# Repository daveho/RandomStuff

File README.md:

# daveho hacks random stuff repository

This is the Git repository for my Random Stuff video series.

The subdirectories contain materials discussed in each episode.

Feedback is welcome, send email to <mailto:david.hovemeyer@gmail.com>

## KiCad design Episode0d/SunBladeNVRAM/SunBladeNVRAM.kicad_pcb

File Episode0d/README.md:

# Random Stuff, Episode 0xD

Link to video: <https://youtu.be/hTzB3pyzDiA>

In this episode, we investigate the
[M48T59Y](https://media.digikey.com/pdf/Data%20Sheets/ST%20Microelectronics%20PDFS/M48T59,Y_V.pdf)
nonvolatile RAM/RTC chip. This device was used in several Sun UltraSPARC workstations,
including a [Sun Blade](https://en.wikipedia.org/wiki/Sun_Blade_(workstation)) 150 which
I want to restore. Sun workstations use an NVRAM chip to store configuration information
such as the MAC address and boot options.  When the battery inside the device runs out,
this configuration information is lost.  Since these devices aren't manufactured any longer,
and haven't been for many years, some kind of replacement is needed.

## Replacement options

The Sun workstations (like my Sun Blade 150) used DIP-package
NVRAM/RTC chips. For the M48T59Y, this is the "-PC" variant.
These are basically just a standard 28-pin DIP device with a
plastic case on top containing the internal battery,
filled with potting compound (picture from EBay):

One replacement option involves grinding away the outer casing and potting compound
in order to expose the connections to the internal battery, soldering
wires to them, and connecting the wires to a coin cell battery holder
(click photos to embiggen):

There are two disadvantages to this approach:

1. It's annoying, time-consuming, and error-prone
2. Unless you're able to disconnect the internal battery embedded in the potting
   compound, the new coin cell battery could be drained trying to charge
   the dead internal battery

What I wanted was a replacement that could be assembled "from scratch", that
would have functionality equivalent to the original device.

Intriguingly, there is a surface-mount version of the chip that has "snap" connectors
for the battery and timing crystal, the "-MH" variant (picture from Amazon Japan):

In theory, you're supposed to use a separate
["SnapHAT" module](https://www.digikey.com/en/products/detail/stmicroelectronics/M4T28-BR12SH1/679615)
containing a battery and crystal, which snaps on top of the chip.
However, this still leaves you with the issue that the battery will
drain eventually, meaning you'll need to buy another SnapHAT, and
eventually these won't be manufactured any more. I really wanted
a solution with a proper coin cell battery holder so that I could
just replace the battery when I needed to.

My thought was that I could design a "stack" of small PCBs with the M48T59Y-70MH1,
a 32.768 kHz watch crystal, and header pins on the lower PCB, a coin cell
battery holder on the upper PCB, and stacking headers to join the two PCBs.
I was actually able to make this work:

Note that there are **significant compromises in the design of the lower PCB**,
and **it is fairly difficult to solder the components on the lower PCB**. I did eventually
arrive at an approach that works to some degree. The following document describes
the assembly steps (and also has the part list):

[Assembling the replacement module](assembly.md)

Also note that the M48T59Y-70MH1 is no longer available new, so you'll need to source
it from the usual secondary channels. I found some for a reasonable price from
a seller on AliExpress.

## Testing and programming

Just having an M48T59Y (either an original with the battery mod or my self-designed
replacement module) still leaves a couple of remaining issues:

* How do you know your M48T59Y is actually working correctly and retaining data
  when power is removed?
* How do you program the initial configuration information (such as the MAC
  address and hostid) into the device?

To address these issues, I designed and built a testing and programming circuit
using an Arduino Nano:

The [SunBladeNVRAMTest](SunBladeNVRAMTest) directory has the KiCad
project for the circuit. There is a [PDF of the schematic](SunBladeNVRAMTest/SunBladeNVRAMTest.pdf)
as well.

There are several Arduino sketches (just load the one you want to use into the
Arduino Nano.)

Before you can use the Arduino sketches, you need to "install" the
[m48t59y](m48t59y) library, which contains common definitions and functions
used by all of the sketches. To do so, either symlink or copy the
contents of the `m48t59y` directory into your `Arduino/libraries`
directory. On my Linux system, I did this by running the commands

```
cd ~/Arduino
mkdir -p libraries
cd libraries
ln -s ~/git/RandomStuff/Epidode0d/m48t59y
```

You should replace `~/git/RandomStuff` with the path to where you checked
out the [RandomStuff](https://github.com/daveho/RandomStuff/) repo.

If you're using Windows, then I believe your `Arduino` directory
will be in your `My Documents` folder. If you create a `libraries` folder
within the `Arduino` directory (if it doesn't already exist) and then copy
the `m48t59y` directory there, that should work.

These are the sketches:

* [Test\_M48T59Y/Test\_M48T59Y.ino](Test_M48T59Y/Test_M48T59Y.ino):
  the test sketch (press GO to start the test; if you hold down LOG when
  you press GO any data validation errors will be logged)
* [Dump\_M48T59Y/Dump\_M49T59Y.ino](Dump_M48T59Y/Dump_M48T59Y.ino):
  dump the NVRAM contents of an M48T59Y to serial output as a
  comma-separated list of hex values. Note that if you're using the
  Arduino 2.x IDE [it's not possible to copy all captured data
  from the serial monitor](https://github.com/arduino/arduino-ide/issues/1081)
  so you'll need to use an external program (e.g., minicom, tio, etc.) to capture
  the output.
* [Restore\_M48T59Y/Restore\_M48T59Y.ino](Restore_M48T59Y/Restore_M48T59Y.ino):
  restore data (stored in a PROGMEM byte array in the sketch) to the M48T59Y.
  Useful to replicate previously dumped data, e.g., reprogramming a device
  after changing the battery. *Hypothetically* you can edit the IDPROM
  data (the source code contains a working dump from a Sun Blade 100)
  and program it to an M48T59Y. The "GO" button writes data to an M48T59Y,
  and the "LOG" button just computes the IDPROM data checksum and
  prints it to the serial output.

Note that all of the sketches use 115200 as the serial baud rate.

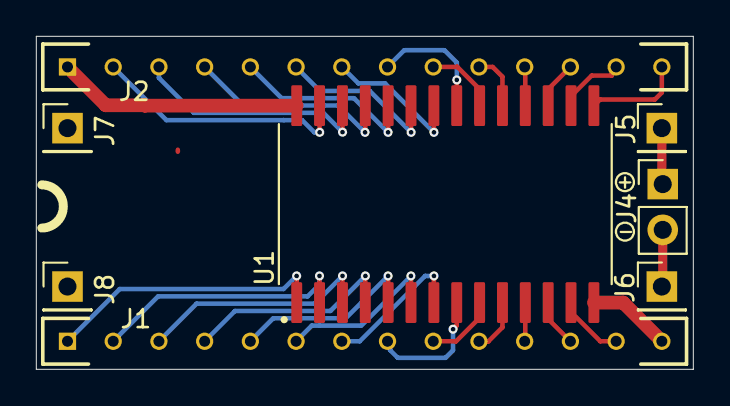
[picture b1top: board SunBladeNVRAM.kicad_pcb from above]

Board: 2 copper layers, 36.5 x 18.5 mm, 8 parts (0 on the bottom side), 30 nets.

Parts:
J1, J2: Conn_01x14_Pin; SAMTEC_BBL-114-T-E
J4: Conn_01x02_Pin; PinHeader_1x02_P2.54mm_Vertical
J5, J6, J7, J8: Conn_01x01_Pin; PinHeader_1x01_P2.54mm_Vertical
U1: M48T59Y-70MH1; M48T59Y-MH

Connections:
unnamed: J1.1, U1.1 (-RST)
unnamed: J1.2, U1.2 (A12)
unnamed: J1.3, U1.3 (A7)
unnamed: J1.4, U1.4 (A6)
unnamed: J1.5, U1.5 (A5)
unnamed: J1.6, U1.6 (A4)
unnamed: J1.7, U1.7 (A3)
unnamed: J1.8, U1.8 (A2)
unnamed: J1.9, U1.9 (A1)
unnamed: J1.10, U1.10 (A0)
unnamed: J1.11, U1.11 (DQ0)
unnamed: J1.12, U1.12 (DQ1)
unnamed: J1.13, U1.13 (DQ2)
unnamed: J1.14, U1.14 (VSS)
unnamed: J2.1, U1.28 (VCC)
unnamed: J2.2, U1.27 (-W)
unnamed: J2.3, U1.26 (-IRQ/FT)
unnamed: J2.4, U1.25 (A8)
unnamed: J2.5, U1.24 (A9)
unnamed: J2.6, U1.23 (A11)
unnamed: J2.7, U1.22 (-G)
unnamed: J2.8, U1.21 (A10)
unnamed: J2.9, U1.20 (-E)
unnamed: J2.10, U1.19 (DQ7)
unnamed: J2.11, U1.18 (DQ6)
unnamed: J2.12, U1.17 (DQ5)
unnamed: J2.13, U1.16 (DQ4)
unnamed: J2.14, U1.15 (DQ3)
unnamed: J4.1, J5.1
unnamed: J4.2, J6.1

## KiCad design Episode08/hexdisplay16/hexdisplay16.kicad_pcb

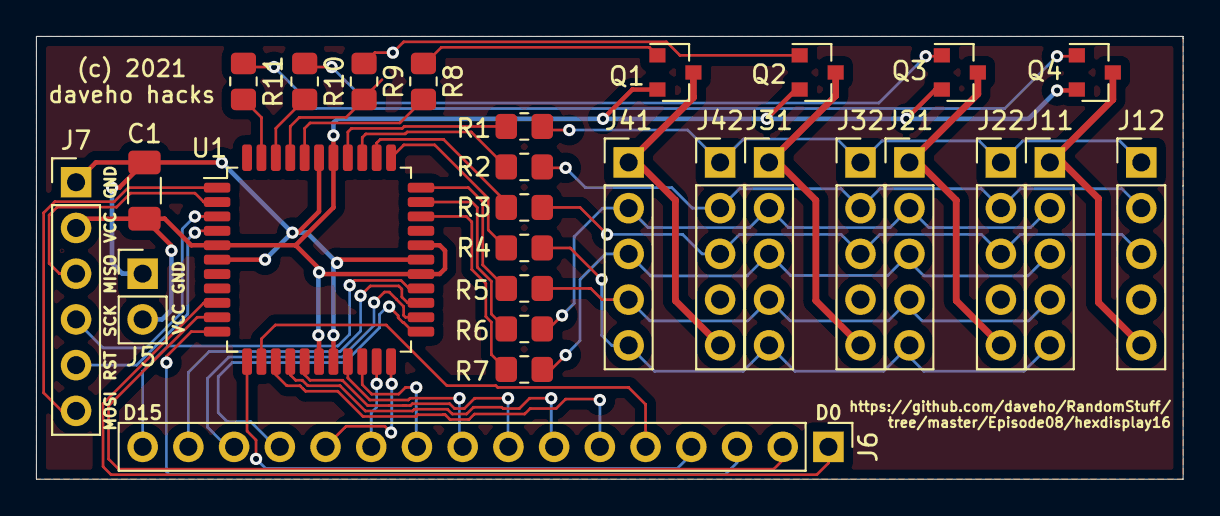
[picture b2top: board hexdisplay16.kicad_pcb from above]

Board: 2 copper layers, 63.7 x 24.6 mm, 28 parts (0 on the bottom side), 48 nets.

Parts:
C1: 100nF; C_1206_3216Metric_Pad1.33x1.80mm_HandSolder
J5: Conn_01x02; PinHeader_1x02_P2.54mm_Vertical
J6: Conn_01x16; PinHeader_1x16_P2.54mm_Vertical
J7: Conn_01x06; PinHeader_1x06_P2.54mm_Vertical
J11, J12, J21, J22, J31, J32, J41, J42: Conn_01x05; PinHeader_1x05_P2.54mm_Vertical
Q1, Q2, Q3, Q4: MMBT3906; SOT-23
R1, R2, R3, R4, R5, R6, R7: 330; R_0805_2012Metric_Pad1.20x1.40mm_HandSolder
R8, R9, R10, R11: 4k7; R_0805_2012Metric_Pad1.20x1.40mm_HandSolder
U1: ATMEGA164A-AU; LQFP-44_10x10mm_P0.8mm

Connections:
/A: J12.1, J22.1, J32.1, J42.1, R1.2
/B: J12.2, J22.2, J32.2, J42.2, R2.2
/C: J12.3, J22.3, J32.3, J42.3, R3.2
/CA1: J41.1, J42.5, Q1.3
/CA2: J31.1, J32.5, Q2.3
/CA3: J21.1, J22.5, Q3.3
/CA4: J11.1, J12.5, Q4.3
/D: J11.5, J21.5, J31.5, J41.5, R4.2
/D0: J6.1, U1.9
/D1: J6.2, U1.10
/D2: J6.3, U1.11
/D3: J6.4, U1.12
/D4: J6.5, U1.13
/D5: J6.6, U1.14
/D6: J6.7, U1.15
/D7: J6.8, U1.16
/D8: J6.9, U1.19
/D9: J6.10, U1.20
/D10: J6.11, U1.21
/D11: J6.12, U1.22
/D12: J6.13, U1.23
/D13: J6.14, U1.24
/D14: J6.15, U1.25
/D15: J6.16, U1.26
/E: J11.4, J21.4, J31.4, J41.4, R5.2
/F: J11.2, J21.2, J31.2, J41.2, R6.2
/G: J11.3, J21.3, J31.3, J41.3, R7.2
/MISO: J7.3, U1.2
/MOSI: J7.6, U1.1
/SCK: J7.4, U1.3
/~RESET: J7.5, U1.4
GND: C1.2, J5.1, J7.1, U1.6, U1.18, U1.28, U1.39
unnamed: Q1.1, R8.1
unnamed: Q2.1, R9.1
unnamed: Q3.1, R10.1
unnamed: Q4.1, R11.1
unnamed: R1.1, U1.37
unnamed: R2.1, U1.36
unnamed: R3.1, U1.35
unnamed: R4.1, U1.34
unnamed: R5.1, U1.33
unnamed: R6.1, U1.32
unnamed: R7.1, U1.31
unnamed: R8.2, U1.40
unnamed: R9.2, U1.41
unnamed: R10.2, U1.42
unnamed: R11.2, U1.43
VCC: C1.1, J5.2, J7.2, Q1.2, Q2.2, Q3.2, Q4.2, U1.5, U1.17, U1.27, U1.29, U1.38

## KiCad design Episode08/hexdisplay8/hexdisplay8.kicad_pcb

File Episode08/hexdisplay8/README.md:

# hexdisplay8

The [KiCad](https://kicad.org/) schematics and PCB designs for the 8-bit
hex display are in this directory.

Parts list:

Component | Description                               | Value  | Footprint
--------- | ----------------------------------------- | ------ | --------------
C1        | ceramic capacitor                         | 100 nF | 1206
R1-R7     | LED segment current limiting resistor     | (a)    | 0805
R8, R9    | transistor base resistor                  | 4.7 kΩ | 0805
Q1, Q2    | MMBT3906 PNP transistor                   | (b)    | SOT-23
U1        | attiny2313a microcontroller               |        | SOIC-20
J11/J12, J21/J22 | common anode hex display                  | (c)    | DIP-10
J3        | 2 pos pin header (breadboard power rails) | (d)    | 2.54mm spacing
J4        | 8 pos pin header (breadboard input)       | (d)    | 2.54mm spacing
J5        | 6 pos pin header (AVR programming header) | (e)    | 2.54mm spacing

(a) The value will depend greatly on the type of LED used in the displays.
220 Ω is reasonable for most standard-brightness LEDs, although a lower value
might be better.  Modern bright LEDs will likely require a larger resistor
value.  In general, 1/8 W rated resistors should be fine.

(b) The transistor should be able to handle at least 100 mA of current.
(Most parts marked as MMBT3906 that I've seen will handle 150 mA or more.)

(c) 0.2" DIP-10 common anode 7-segment displays, specifically
[SUNLIGHT SLR0361DBA3BD-4.0](https://lcsc.com/product-detail/Led-Segment-Display_SUNLIGHT-SLR0361DBA3BD-4-0_C225953.html).  The common anodes should be on pins 1 and 6.
(And you should check to make sure the cathode pins are in the right places.)

(d) I prefer machined pin headers, since these will be inserted into the
breadboard, and the thinner pins are less likely to deform the metal clips
inside the breadboard.

(e) I use the cheaper square profile pin headers for this connector, since
it's only used when programming the microcontroller.

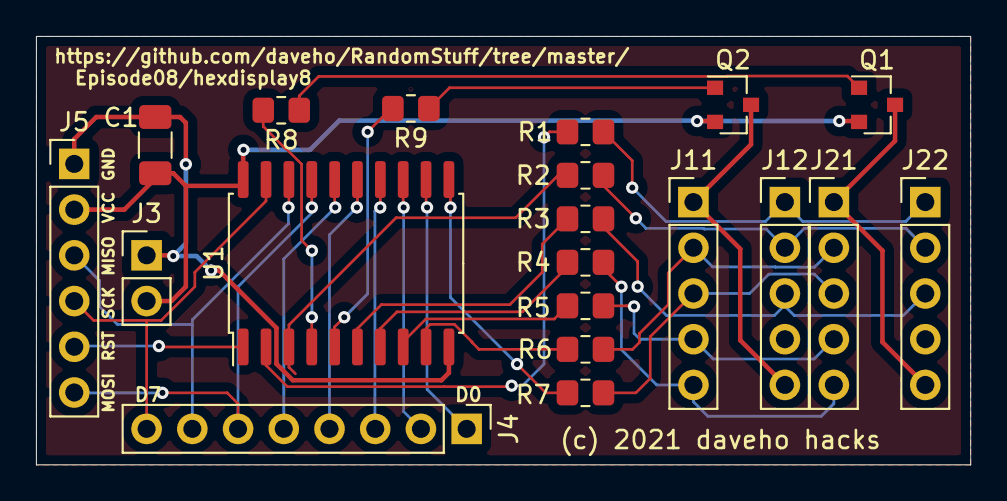
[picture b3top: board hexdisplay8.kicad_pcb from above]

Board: 2 copper layers, 51.9 x 23.8 mm, 20 parts (0 on the bottom side), 31 nets.

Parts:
C1: 100nF; C_1206_3216Metric_Pad1.33x1.80mm_HandSolder
J3: Conn_01x02; PinHeader_1x02_P2.54mm_Vertical
J4: Conn_01x08; PinHeader_1x08_P2.54mm_Vertical
J5: Conn_01x06; PinHeader_1x06_P2.54mm_Vertical
J11, J12, J21, J22: Conn_01x05; PinHeader_1x05_P2.54mm_Vertical
Q1, Q2: MMBT3906; SOT-23
R1, R2, R3, R4, R5, R6, R7: 330; R_0805_2012Metric_Pad1.20x1.40mm_HandSolder
R8, R9: 4k7; R_0805_2012Metric_Pad1.20x1.40mm_HandSolder
U1: ATTINY2313A-SU; SOIC-20W_7.5x12.8mm_P1.27mm

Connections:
/A: J12.1, J22.1, R1.1
/B: J12.2, J22.2, R2.1
/C: J12.3, J22.3, R3.1
/CA1: J21.1, J22.5, Q1.3
/CA2: J11.1, J12.5, Q2.3
/D: J11.5, J21.5, R4.1
/D0: J4.1, U1.12
/D1: J4.2, U1.13
/D2: J4.3, U1.14
/D3: J4.4, U1.15
/D4: J4.5, U1.16
/D5: J4.6, J5.6, U1.17
/D6: J4.7, J5.3, U1.18
/D7: J4.8, J5.4, U1.19
/E: J11.4, J21.4, R5.1
/F: J11.2, J21.2, R6.1
/G: J11.3, J21.3, R7.1
/~RESET: J5.5, U1.1
GND: C1.2, J3.1, J5.1, U1.10
unnamed: Q1.1, R8.1
unnamed: Q2.1, R9.1
unnamed: R1.2, U1.2
unnamed: R2.2, U1.3
unnamed: R3.2, U1.6
unnamed: R4.2, U1.7
unnamed: R5.2, U1.8
unnamed: R6.2, U1.9
unnamed: R7.2, U1.11
unnamed: R8.2, U1.4
unnamed: R9.2, U1.5
VCC: C1.1, J3.2, J5.2, Q1.2, Q2.2, U1.20

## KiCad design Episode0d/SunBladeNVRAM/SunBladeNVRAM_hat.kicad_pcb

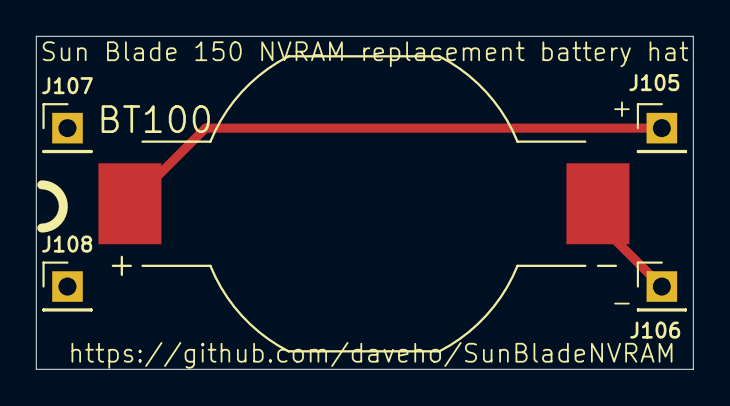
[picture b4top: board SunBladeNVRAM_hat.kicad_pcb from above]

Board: 2 copper layers, 36.5 x 18.5 mm, 5 parts (0 on the bottom side), 2 nets.

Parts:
BT100: BU1632SM-JJ-GTR; BAT_BU1632SM-JJ-GTR
J105, J106, J107, J108: Conn_01x01_Pin; PinHeader_1x01_P2.54mm_Vertical

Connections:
unnamed: BT100.+, J105.1
unnamed: BT100.-, J106.1

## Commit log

2019-12-08 schematics and code for LED blink example
2019-12-08 shift register demo
2019-12-08 in/out demo program
2019-12-08 minor tweak to README.md
2019-12-09 added readme files for hw and fw directories
2019-12-09 link to video
2019-12-12 80C32 demo circuit
2019-12-12 copied Blink_LED program for testing with 80C32 circuit
2019-12-12 copied InOut program from Episode01
2019-12-15 AVR version of InOut program
2019-12-21 final changes to experiment firmware code
2019-12-21 added README.md files
2019-12-21 mention at89c2051 circuit
2019-12-21 use grammar
2019-12-22 compiled hex files
2019-12-22 add info about SDCC version
2019-12-22 fixed file names
2020-06-06 README for Episode 04
2020-06-06 fix typo
2020-06-06 added link to video
2020-06-06 a bit more about OBS Studio
2020-12-21 start working on 8048 experiments
2020-12-21 add decoupling caps, use 74HCT573 for addr latch
2020-12-24 initial 8048 test programs
2020-12-24 added more info
2020-12-24 update to kicad project file
2020-12-24 LED blink and button press programs working
2020-12-24 pdf schematics
2020-12-24 link to pdf schematics
2020-12-25 timer interrupt test program
2020-12-25 holiday LED blink program
2020-12-25 project is done, next update will be the video URL
2021-02-28 new version of 16 bit hex display
    This version uses more "modern" DIP-10 common anode
    1 digit displays. Plan is to use HDSP-F501 high-efficiency
    green displays. These should be much brighter than the
    standard efficiency LED displays I used previously.
    Will need to test to determine optimum values for the
    current limiting resistors.
2021-03-06 only use local symbol libraries
2021-03-06 fix pinout of display modules
2021-03-06 use proper DIP-10 connectors for hex displays
2021-03-06 fix no connects (only for decimal point cathode)
2021-03-06 fix common anode lines
2021-03-06 assign packages
2021-03-06 generate netlist
2021-03-06 started working on pcb layout
2021-03-07 component placement is reasonable?
    Now need to do routing.
2021-03-07 started the signal routing
2021-03-07 finishing routing signals
2021-03-07 added ground planes
2021-03-07 schematic for 8 bit hex display
2021-03-07 use correct package for attiny2313a
2021-03-07 fix power connector
2021-03-07 placed components
2021-03-07 routed signals
2021-03-07 added additional silkscreen markings
2021-03-07 ignore fp-info-cache
2021-03-07 minor silkscreen adjustment
2021-03-07 generate gerber files
2021-03-07 updates due to generating gerbers
2021-03-07 generate gerbers
2021-03-07 name gerber zipfiles appropriately
2021-03-21 start working on hexdisplay8 firmware
2021-03-21 added some comments and added .gitignore
2021-03-21 rename hexdisplay08_fw to hexdisplay8_fw for consistency
2021-03-21 fix comment for consistency
2021-03-21 more renaming for consistency
2021-03-21 various fixes
2021-03-21 working on firmware for hexdisplay16
2021-03-21 fix program name
2021-03-21 disable JTAG
2021-04-10 fix output pins used to control CA1 and CA2
    Firmware appears to work correctly now! Display
    multiplexing seems to be working very well (no ghosting
    of segments.)
2021-04-17 pdf of hexdisplay8 schematic
2021-04-24 displays were reversed on PCB, update schematic and firmware
    Also, increase the refresh rate to avoid on-camera
    flickering.
2021-04-24 change delay from 8 ms to 2 ms
    This eliminates flickering when recorded on 60 fps video.
2021-04-25 minor schematic updates, regenerated PDFs
2021-04-25 use CERN Open Source Hardware license v2 (permissive)
2021-04-25 working on readme files
2021-04-25 README.md for hexdisplay16, minor schematic/README updates
2021-04-25 prepare to link to video
2021-05-08 7 segment display test program, incr. refresh rate
2021-05-08 added README.md and photo
2021-05-08 better picture
2021-05-08 minor clarification
2021-05-08 mention Arduino test prog and firmware updates
2021-05-20 ultimate versions of hex displays?
2021-05-20 regenerate gerbers
    JLCPCB is giving me issues. Probably will just order and
    hope for the best, the boards seem file when viewed in KiCad's
    gerber viewer.
2021-07-05 rename Episode08 as Episode09
2021-07-05 updated URL on silkscreen
    The hex display episode will be Random Stuff #9.
    Unfortunately, the actual PCBs say Episode 08. Oh well.
2021-07-05 changed to support USBtinyISP
2021-07-06 updated Makefile: support USBtiny, atmega324pa
2021-07-24 picture, updates to READMEs
2021-07-24 fix link to picture
2021-07-24 actually fix image link this time
2021-07-24 link to firmware, minor parts list updates
2025-01-05 start to add Episode 0A content
2025-01-05 fix image links
2025-01-05 fix links to sketches
2025-01-05 module design, started assembly instructions
2025-01-05 disclaimer
2025-01-05 note about sourcing battery holder
2025-01-05 fix link to KiCad project
2025-01-05 more intermediate step photos
2025-01-05 use correct article
2025-01-06 remove xtal from bottom PCB
    There's no point in wiring the xtal to the bottom PCB
    since it can be soldered directly to the snap connectors
    on the M48T59Y-70MH1.
    Also, increase the size of the "notch" arc on the bottom
    PCB, and add it to the top PCB.
2025-01-06 link on silkscreen is actually fine
2025-01-06 have read/write configure bus dir automatically
2025-01-06 test that time/date values can be read back
2025-01-06 implemented sketch to program IDPROM info
2025-01-06 fix cut and paste error
2025-01-07 factored out common code into a library
2025-01-07 note about installing the Arduino library
2025-01-07 mention test circuit KiCad project
    Also, include a PDF of the test circuit schematic.
2025-01-07 fix minor typo
2025-01-07 sketch to dump NVRAM contents
2025-01-07 restore sketch
2025-01-07 ignore all dump*.txt files
2025-01-07 use data from actual Sun Blade 100 NVRAM
2025-01-08 use fast serial (115200 bps)
2025-01-08 suggest tio to capture serial output
2025-01-08 updated Sun Blade 100 NVRAM contents
2025-01-09 added functionality to compute IDPROM checksum
    Pressing "LOG" will do this. That in theory allows
    a usage scenario where you modify the IDPROM data,
    upload the sketch, press LOG to recompute the
    checksum, then update the checksum, and hopefully
    you have valid NVRAM data to write to an M48T59Y.
2025-01-09 Remove the Program_M48T59Y sketch
    The Restore_M48T59Y sketch is (I think) a better option,
    since it programs actual known-working NVRAM data.
2025-01-09 mention tio program
2025-01-09 latest should be episode D
2025-01-09 script to convert dump output to binary

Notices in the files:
Episode08/hexdisplay8/hexdisplay8.kicad_pcb:
(c) 2021 daveho hacks
Episode0d/SunBladeNVRAM/SunBladeNVRAM.kicad_pcb:
(c) 2024, daveho hacks
